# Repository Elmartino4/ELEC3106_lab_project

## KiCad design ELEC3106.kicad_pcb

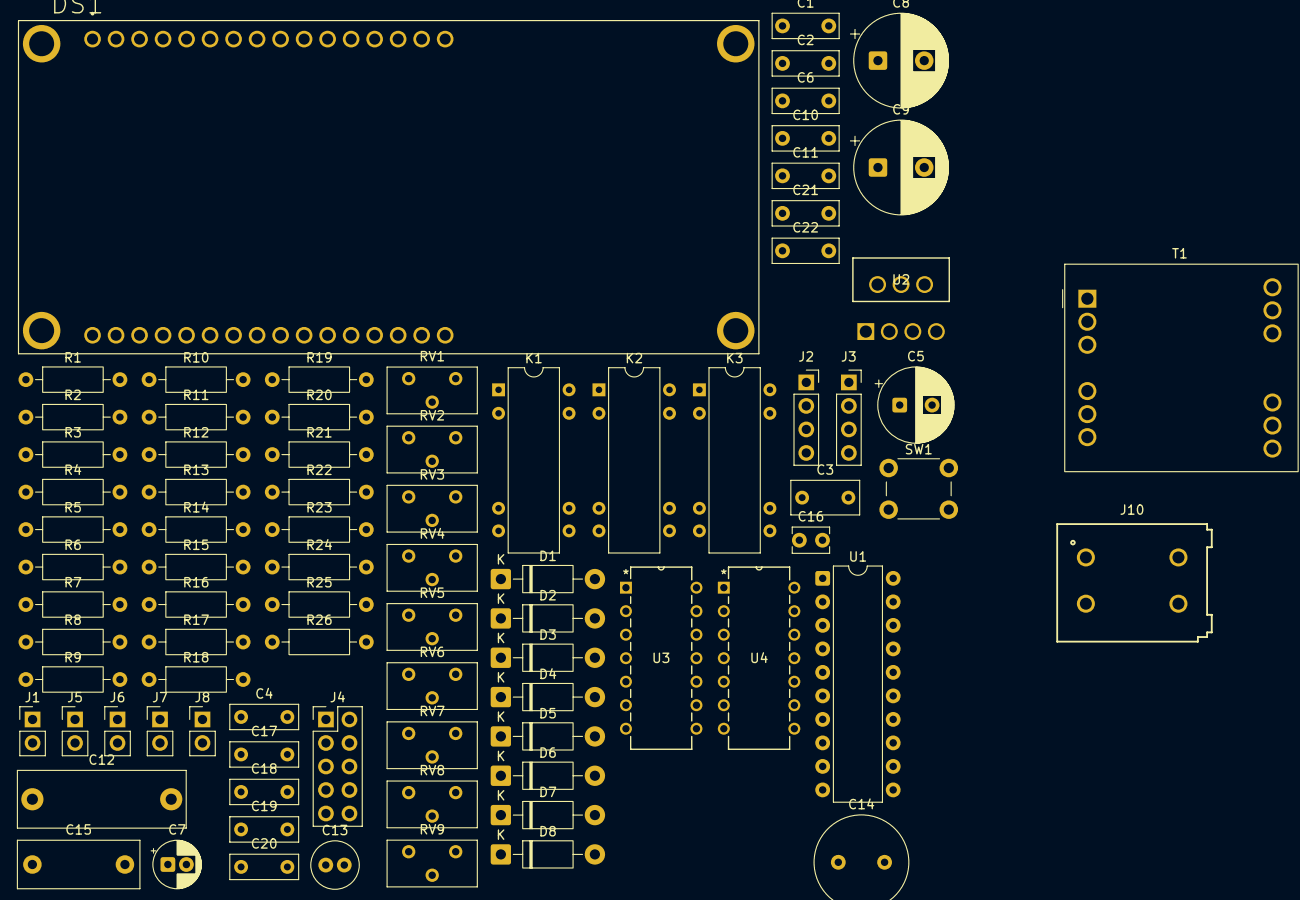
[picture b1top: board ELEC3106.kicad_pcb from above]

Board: 2 copper layers, 84 parts (0 on the bottom side), 67 nets, no tracks yet.

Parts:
C1, C2, C6, C10, C11, C21, C22: 100n; C_Rect_L7.0mm_W2.5mm_P5.00mm
C3: 470n; C_Rect_L7.2mm_W3.5mm_P5.00mm
C4, C17, C18, C19, C20: 50n; C_Rect_L7.2mm_W2.5mm_P5.00mm
C5: 100u; CP_Radial_D8.0mm_P3.50mm
C7: 1u; CP_Radial_D5.0mm_P2.00mm
C8, C9: 330u; CP_Radial_D10.0mm_P5.00mm
C12: 180n; C_Rect_L18.0mm_W6.0mm_P15.00mm_FKS3_FKP3
C13: 3.3u; C_Radial_D5.0mm_H11.0mm_P2.00mm
C14: 47u; C_Radial_D10.0mm_H16.0mm_P5.00mm
C15: 10n; C_Rect_L13.0mm_W5.0mm_P10.00mm_FKS3_FKP3_MKS4
C16: 300p; C_Disc_D3.8mm_W2.6mm_P2.50mm
D1, D2, D3: 1N4732; D_DO-41_SOD81_P10.16mm_Horizontal
D4, D5, D6, D7, D8: 1N5819; D_DO-41_SOD81_P10.16mm_Horizontal
DS1: NHD-0216K1Z-NSW-BBW-L; NHD_NHD-0216K1Z-NSW-BBW-L
J1: MCU_Supply; PinHeader_1x02_P2.54mm_Vertical
J2: Digital_Signals; PinSocket_1x04_P2.54mm_Vertical
J3: Analogue_Signals; PinSocket_1x04_P2.54mm_Vertical
J4: Prog; PinHeader_2x05_P2.54mm_Vertical
J5: Display_supply; PinHeader_1x02_P2.54mm_Vertical
J6: Boost_Supply; PinHeader_1x02_P2.54mm_Vertical
J7, J8: Boost_Output; PinHeader_1x02_P2.54mm_Vertical
J10: 691411810002; term
K1, K2, K3: Reed; Relay_StandexMeder_DIP_LowProfile
R1, R3, R14, R15, R16, R17, R18, R19, R20, R23, R24: 10k; R_Axial_DIN0207_L6.3mm_D2.5mm_P10.16mm_Horizontal
R2: 2.4k; R_Axial_DIN0207_L6.3mm_D2.5mm_P10.16mm_Horizontal
R4, R5, R6, R7, R8, R9, R10: 560; R_Axial_DIN0207_L6.3mm_D2.5mm_P10.16mm_Horizontal
R11: 2M; R_Axial_DIN0207_L6.3mm_D2.5mm_P10.16mm_Horizontal
R12: 100k; R_Axial_DIN0207_L6.3mm_D2.5mm_P10.16mm_Horizontal
R13: 5.1k; R_Axial_DIN0207_L6.3mm_D2.5mm_P10.16mm_Horizontal
R21: 4.7k; R_Axial_DIN0207_L6.3mm_D2.5mm_P10.16mm_Horizontal
R22: 12k; R_Axial_DIN0207_L6.3mm_D2.5mm_P10.16mm_Horizontal
R25, R26: 1M; R_Axial_DIN0207_L6.3mm_D2.5mm_P10.16mm_Horizontal
RV1, RV2: 10k_sig; Potentiometer_Bourns_3296Y_Vertical
RV3: 10k_rail; Potentiometer_Bourns_3296Y_Vertical
RV4: 10k_disp; Potentiometer_Bourns_3296Y_Vertical
RV5: 1M; Potentiometer_Bourns_3296Y_Vertical
RV6: 50k; Potentiometer_Bourns_3296Y_Vertical
RV7: 2k; Potentiometer_Bourns_3296Y_Vertical
RV8: 10k_Diff; Potentiometer_Bourns_3296Y_Vertical
RV9: 10k_freq; Potentiometer_Bourns_3296Y_Vertical
SW1: Reset; SW_PUSH_6mm_H5mm
T1: EE20_10_6_L22.2W25H16_12PINS_750314624; T_Wurth_WE-IBTI-EE20_10_6_L22.2W25H16_12PINS
U1: ATtiny861A-P; DIP-20_W7.62mm
U2: LM2586T-ADJ/NOPB; LM2586T-ADJ
U3, U4: TLE2074IN

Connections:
+5V: DS1.15_1, DS1.15_2, J1.1, J4.2, J5.1, J6.2, R1.1
+15V: C10.2, C11.2, J7.1, U3.4 (VCC+), U4.4 (VCC+)
-15V: C21.1, C22.1, J8.1, U3.11 (VCC-), U4.11 (VCC-)
D_cap: C4.1, D1.1 (K), J2.1, R3.1, R24.2, U1.18 (PA2)
GND: C1.2, C2.2, C3.2, C4.2, C5.2, C6.2, C7.2, C8.2, C9.2, C10.1, C11.1, C17.2, C18.2, C19.2, C20.2, C21.2, C22.2, D1.2 (A), D2.2 (A), D3.2 (A), DS1.1_1 (VSS), DS1.1_2 (VSS), DS1.16_1, DS1.16_2, DS1.S1 (SHIELD), DS1.S2 (SHIELD), DS1.S3 (SHIELD), DS1.S4 (SHIELD), J4.4, J4.6, J4.8, J4.10, K1.2, K2.2, K3.2, R3.2, R18.1, R21.1, R25.2, R26.2, RV1.1, RV2.1, RV3.3, RV4.1, SW1.1, T1.7, T1.14, U1.6 (GND), U1.16 (AGND), U2.4 (GND), U3.3 (1IN+), U3.5 (2IN+), U4.3 (1IN+), U4.5 (2IN+)
unnamed: C3.1, R2.2
unnamed: C12.1, K1.7
unnamed: C12.2, RV5.3
unnamed: C13.1, K2.7
unnamed: C13.2, RV6.3
unnamed: C14.1, K3.7
unnamed: C14.2, RV7.3
unnamed: D2.1 (K), RV1.2, U1.20 (PA0)
unnamed: D3.1 (K), RV2.2, U1.19 (PA1)
unnamed: D4.2 (A), RV3.1, T1.12
unnamed: C8.1, D4.1 (K), J7.2
unnamed: C9.1, D5.2 (A), J8.2
unnamed: D5.1 (K), T1.9
unnamed: D6.2 (A), U3.14 (4OUT)
unnamed: D7.2 (A), U3.8 (3OUT)
unnamed: D8.2 (A), R23.2, U4.8 (3OUT)
unnamed: C17.1, D8.1 (K), R24.1
unnamed: DS1.11_1 (DB4), DS1.11_2 (DB4), R4.2
unnamed: DS1.12_1 (DB5), DS1.12_2 (DB5), R6.2
unnamed: DS1.13_1 (DB6), DS1.13_2 (DB6), R8.2
unnamed: DS1.14_1 (DB7), DS1.14_2 (DB7), R10.2
unnamed: DS1.6_1 (E), DS1.6_2 (E), R5.2
unnamed: DS1.4_1 (RS), DS1.4_2 (RS), R7.2
unnamed: DS1.5_1 (R/W), DS1.5_2 (R/W), R9.2
unnamed: C1.1, C2.1, J1.2, U1.5 (VCC), U1.15 (AVCC)
unnamed: J4.1, R4.1, U1.1 (PB0)
unnamed: J4.5, R1.2, SW1.2, U1.10 (~RESET/PB7)
unnamed: J4.7, R8.1, U1.3 (PB2)
unnamed: J4.9, R6.1, U1.2 (PB1)
unnamed: C5.1, C7.1, J6.1, T1.4, T1.5, U2.7 (Vin)
unnamed: K1.8, R11.1
unnamed: K2.8, R12.1
unnamed: K3.8, R13.1
unnamed: R10.1, U1.4 (PB3)
unnamed: R5.1, U1.9 (PB6)
unnamed: R9.1, U1.7 (XTAL1/PB4)
unnamed: R7.1, U1.8 (XTAL2/PB5)
unnamed: R2.1, U2.2 (Comp)
unnamed: RV3.2, U2.3 (Feedback)
unnamed: T1.2, T1.3, U2.5 (Switch)
unnamed: C15.2, C16.2, RV8.1, RV8.2, U3.2 (1IN-)
unnamed: C16.1, R19.2, RV8.3, U3.1 (1OUT)
unnamed: J10.2, J10.A2, K1.1, K1.14, K2.1, K2.14, K3.1, K3.14, U3.6 (2IN-)
unnamed: R20.2, U3.10 (3IN+)
unnamed: R19.1, U3.12 (4IN+)
unnamed: R14.2, U4.2 (1IN-)
unnamed: R16.2, U4.1 (1OUT)
unnamed: R17.2, U4.6 (2IN-)
unnamed: R15.1, U4.7 (2OUT)
unnamed: R17.1, R18.2, U4.10 (3IN+)
unnamed: R16.1, R23.1, U4.9 (3IN-)
unnamed: R21.2, R22.1, U4.12 (4IN+)
unnamed: C20.1, RV9.1, U4.13 (4IN-)
RANGE_1: J2.4, K1.6, U1.17 (AREF/PA3)
RANGE_2: J2.3, K2.6, U1.14 (PA4)
RANGE_3: J2.2, K3.6, U1.13 (PA5)
V0: DS1.3_1 (V0), DS1.3_2 (V0), RV4.2
VDD: C6.1, DS1.2_1 (VDD), DS1.2_2 (VDD), J5.2, RV4.3
V_Cap: C18.1, D6.1 (K), J3.3, R25.1, RV1.3, U3.13 (4IN-)
V_Comp: C15.1, J3.1, J10.1, J10.A1, R11.2, R12.2, R13.2, R15.2, R20.1, U3.7 (2OUT)
V_Res: C19.1, D7.1 (K), J3.4, R26.1, RV2.3, U3.9 (3IN-)
V_Sq: J3.2, R14.1, R22.2, RV5.1, RV5.2, RV6.1, RV6.2, RV7.1, RV7.2, RV9.2, RV9.3, U4.14 (4OUT)
